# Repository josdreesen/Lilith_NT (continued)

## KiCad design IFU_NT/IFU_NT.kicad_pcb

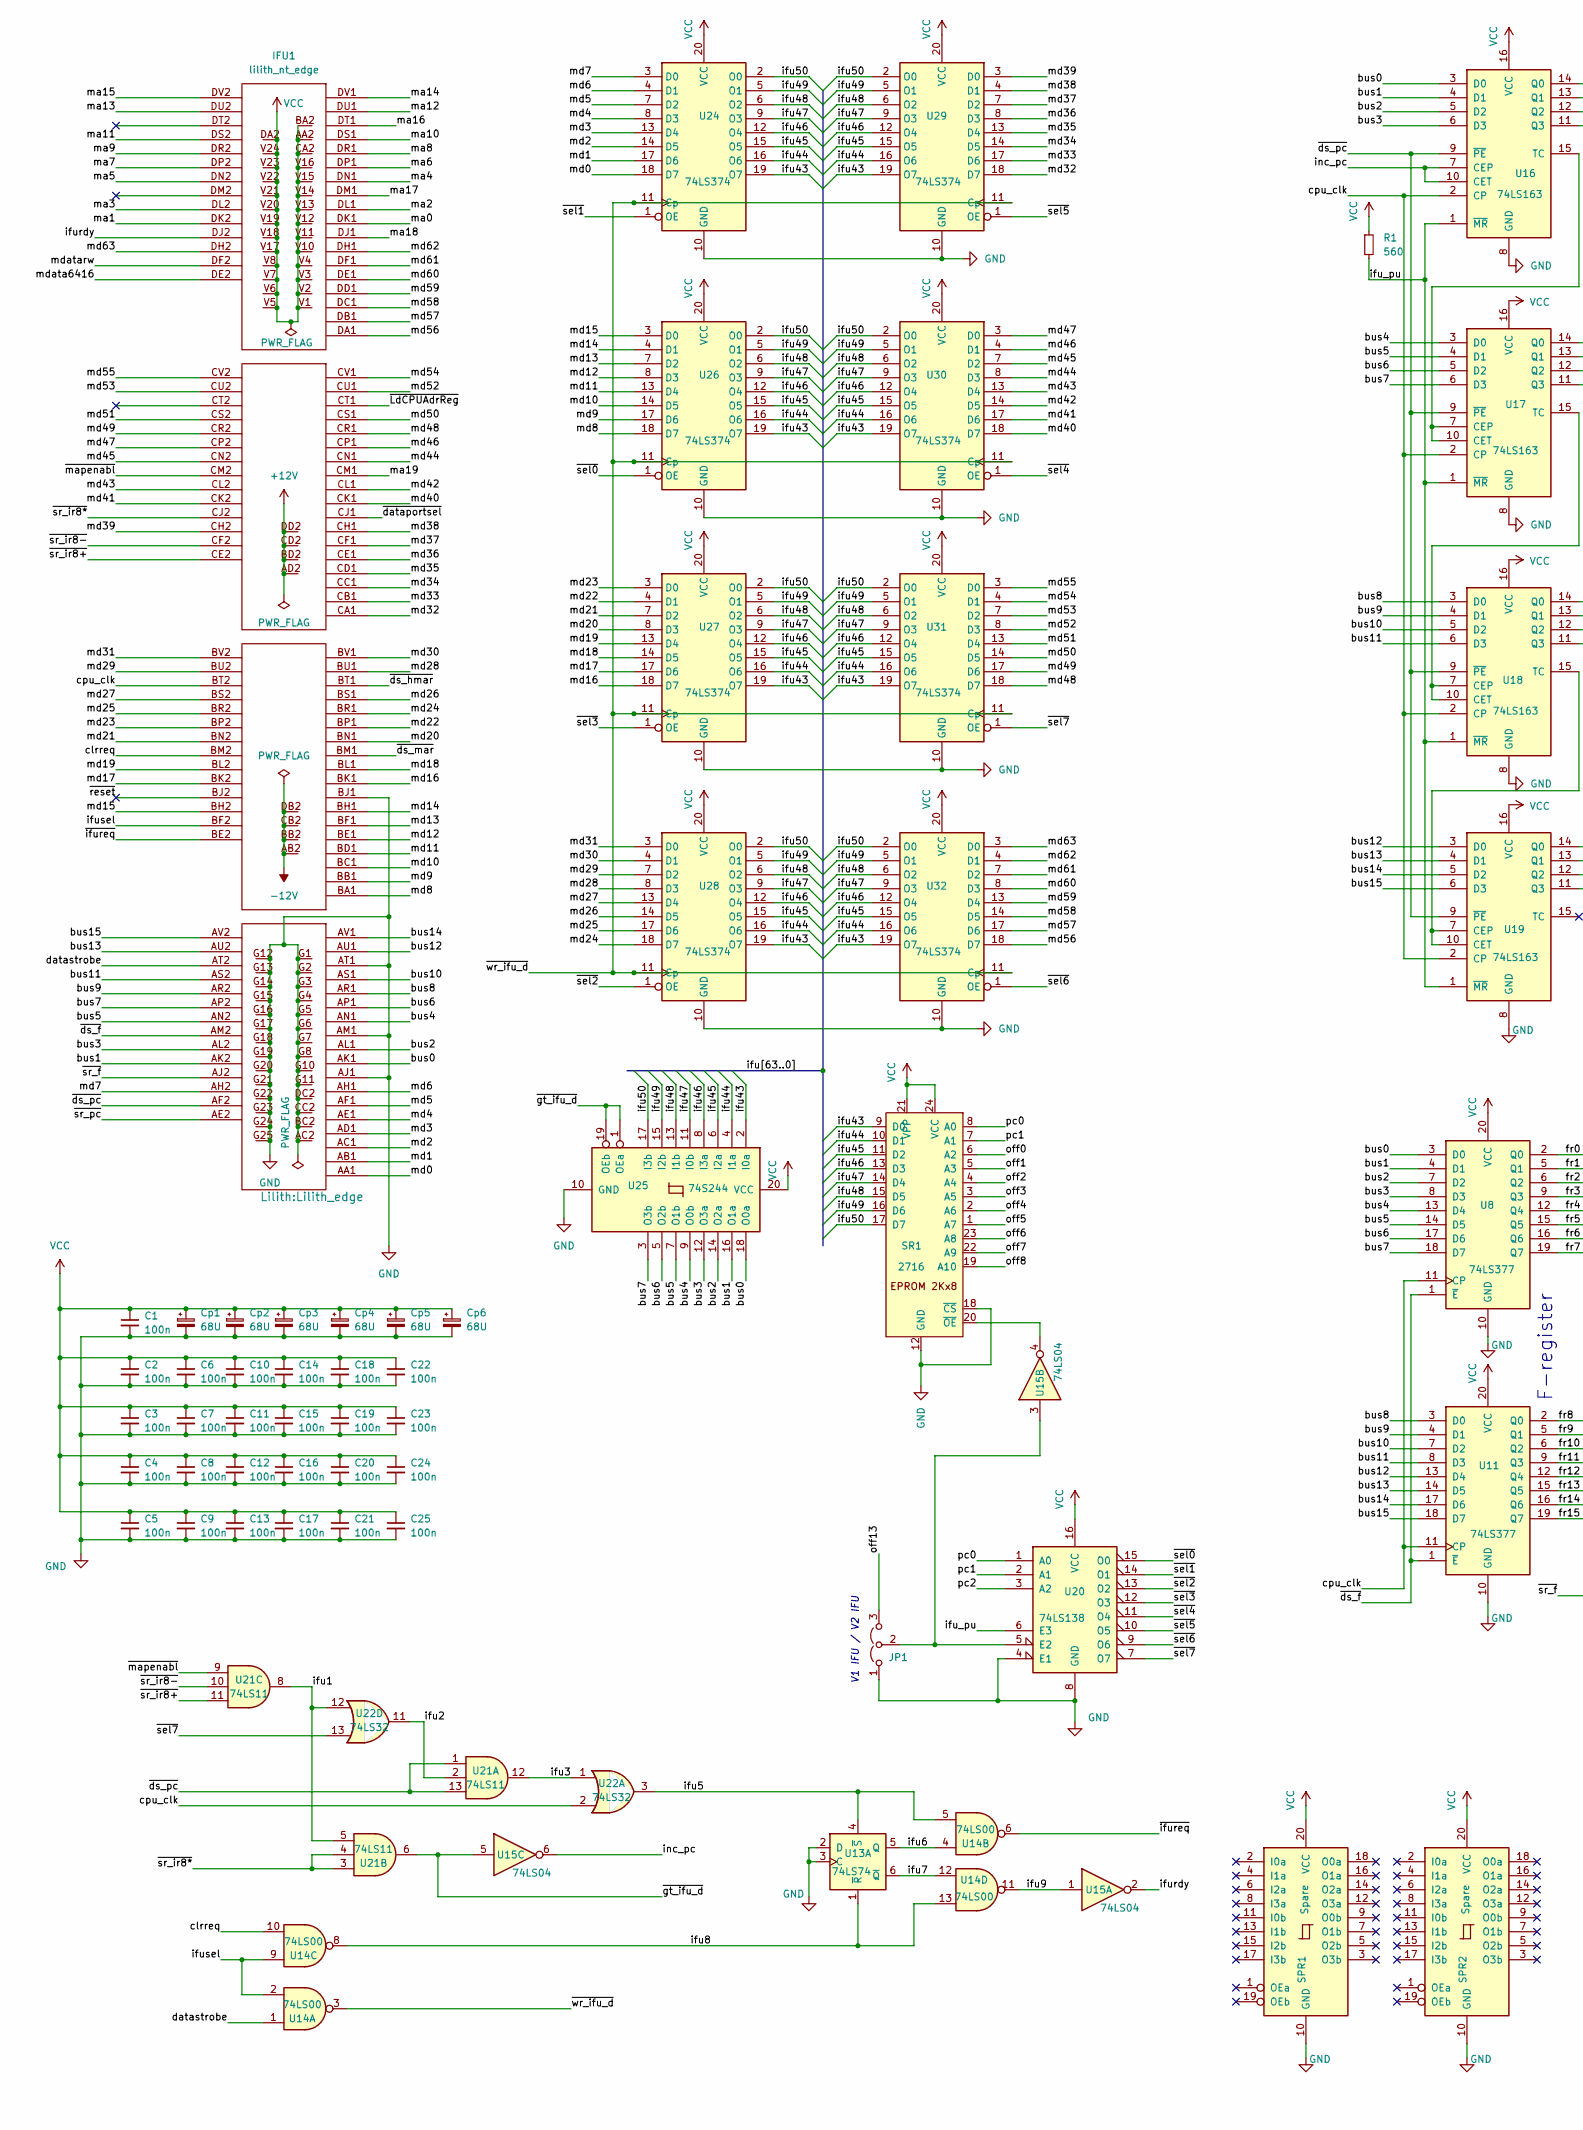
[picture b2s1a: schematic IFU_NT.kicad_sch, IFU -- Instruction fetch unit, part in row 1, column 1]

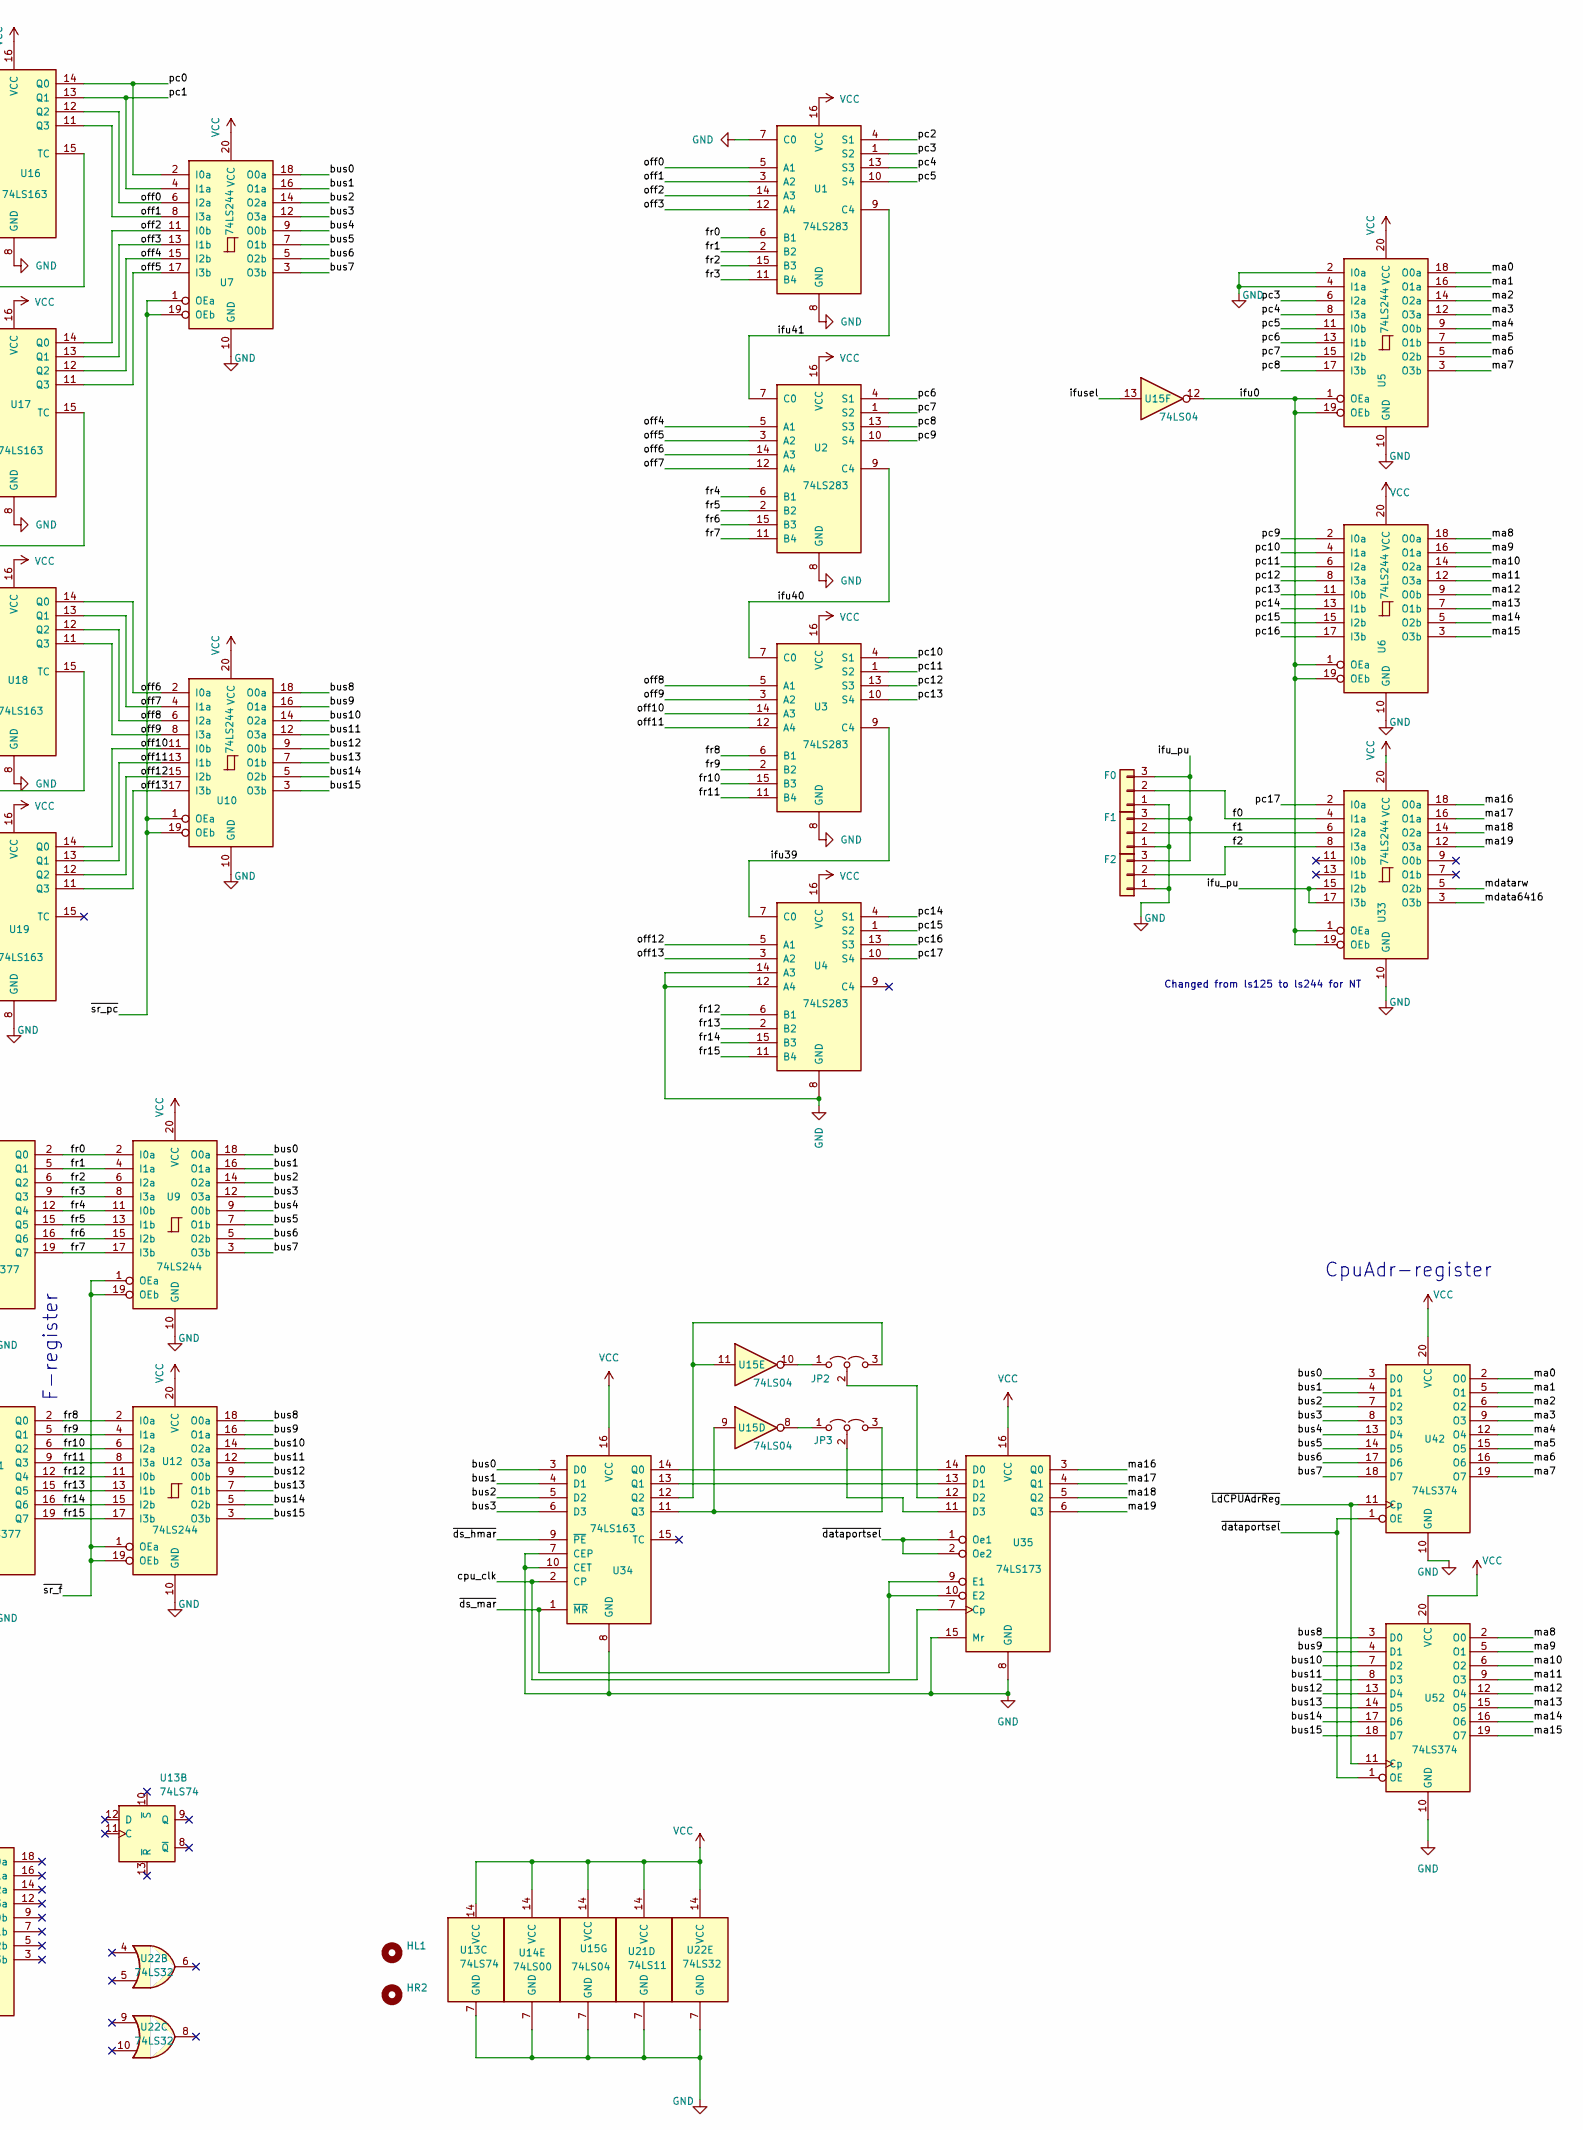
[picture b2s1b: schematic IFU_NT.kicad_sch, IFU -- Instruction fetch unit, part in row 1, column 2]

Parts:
C1, C2, C3, C4, C5, C6, C7, C8, C9, C10, C11, C12, C13, C14, C15, C16, C17, C18, C19, C20, C21, C22, C23, C24, C25: 100n; C_1206_3216Metric_Pad1.33x1.80mm_HandSolder
Cp1, Cp2, Cp3, Cp4, Cp5, Cp6: 68U; CP_PHP
F0, F1, F2: Conn_01x03; PinHeader_1x03_P2.54mm_Vertical
HL1: MountingHole; Handle
HR2: MountingHole; Handle
IFU1: lilith_nt_edge; Lilith_edge
JP1: Jumper_3_Open; PinSocket_1x03_P2.54mm_Vertical
JP2, JP3: Jumper_3_Open; PinHeader_1x03_P2.00mm_Vertical
R1: 560; R_Axial_DIN0207_L6.3mm_D2.5mm_P10.16mm_Horizontal
SPR1, SPR2: Spare; DIP-20_W7.62mm
SR1: 2716; DIP-24_W15.24mm_Socket
U1, U2, U3, U4: 74LS283; DIP-16_W7.62mm
U5, U6, U7, U9, U10, U12, U33: 74LS244; DIP-20_W7.62mm
U8, U11: 74LS377; DIP-20_W7.62mm
U13: 74LS74; DIP-14_W7.62mm
U14: 74LS00; DIP-14_W7.62mm
U15: 74LS04; DIP-14_W7.62mm
U16, U17, U18, U19, U34: 74LS163; DIP-16_W7.62mm
U20: 74LS138; DIP-16_W7.62mm
U21: 74LS11; DIP-14_W7.62mm
U22: 74LS32; DIP-14_W7.62mm
U24, U26, U27, U28, U29, U30, U31, U32, U42, U52: 74LS374; DIP-20_W7.62mm
U25: 74S244; DIP-20_W7.62mm
U35: 74LS173; DIP-16_W7.62mm

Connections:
+12V: IFU1.AD2, IFU1.BD2, IFU1.CD2, IFU1.DD2
-12V: IFU1.AB2, IFU1.BB2, IFU1.CB2, IFU1.DB2
/bus0: IFU1.AK1, U7.18 (O0a), U8.3 (D0), U9.18 (O0a), U16.3 (D0), U25.18 (O0a), U34.3 (D0), U42.3 (D0)
/bus1: IFU1.AK2, U7.16 (O1a), U8.4 (D1), U9.16 (O1a), U16.4 (D1), U25.16 (O1a), U34.4 (D1), U42.4 (D1)
/bus2: IFU1.AL1, U7.14 (O2a), U8.7 (D2), U9.14 (O2a), U16.5 (D2), U25.14 (O2a), U34.5 (D2), U42.7 (D2)
/bus3: IFU1.AL2, U7.12 (O3a), U8.8 (D3), U9.12 (O3a), U16.6 (D3), U25.12 (O3a), U34.6 (D3), U42.8 (D3)
/bus4: IFU1.AN1, U7.9 (O0b), U8.13 (D4), U9.9 (O0b), U17.3 (D0), U25.9 (O0b), U42.13 (D4)
/bus5: IFU1.AN2, U7.7 (O1b), U8.14 (D5), U9.7 (O1b), U17.4 (D1), U25.7 (O1b), U42.14 (D5)
/bus6: IFU1.AP1, U7.5 (O2b), U8.17 (D6), U9.5 (O2b), U17.5 (D2), U25.5 (O2b), U42.17 (D6)
/bus7: IFU1.AP2, U7.3 (O3b), U8.18 (D7), U9.3 (O3b), U17.6 (D3), U25.3 (O3b), U42.18 (D7)
/bus8: IFU1.AR1, U10.18 (O0a), U11.3 (D0), U12.18 (O0a), U18.3 (D0), U52.3 (D0)
/bus9: IFU1.AR2, U10.16 (O1a), U11.4 (D1), U12.16 (O1a), U18.4 (D1), U52.4 (D1)
/bus10: IFU1.AS1, U10.14 (O2a), U11.7 (D2), U12.14 (O2a), U18.5 (D2), U52.7 (D2)
/bus11: IFU1.AS2, U10.12 (O3a), U11.8 (D3), U12.12 (O3a), U18.6 (D3), U52.8 (D3)
/bus12: IFU1.AU1, U10.9 (O0b), U11.13 (D4), U12.9 (O0b), U19.3 (D0), U52.13 (D4)
/bus13: IFU1.AU2, U10.7 (O1b), U11.14 (D5), U12.7 (O1b), U19.4 (D1), U52.14 (D5)
/bus14: IFU1.AV1, U10.5 (O2b), U11.17 (D6), U12.5 (O2b), U19.5 (D2), U52.17 (D6)
/bus15: IFU1.AV2, U10.3 (O3b), U11.18 (D7), U12.3 (O3b), U19.6 (D3), U52.18 (D7)
/clrreq: IFU1.BM2, U14.10
/cpu_clk: IFU1.BT2, U8.11 (CP), U11.11 (CP), U16.2 (CP), U17.2 (CP), U18.2 (CP), U19.2 (CP), U22.2, U34.2 (CP), U35.7 (Cp)
/datastrobe: IFU1.AT2, U14.1
/f0: F0.2, U33.4 (I1a); also elsewhere on the board
/f1: F1.2, U33.6 (I2a); also elsewhere on the board
/f2: F2.2, U33.8 (I3a); also elsewhere on the board
/fr0: U1.6 (B1), U8.2 (Q0), U9.2 (I0a)
/fr1: U1.2 (B2), U8.5 (Q1), U9.4 (I1a)
/fr2: U1.15 (B3), U8.6 (Q2), U9.6 (I2a)
/fr3: U1.11 (B4), U8.9 (Q3), U9.8 (I3a)
/fr4: U2.6 (B1), U8.12 (Q4), U9.11 (I0b)
/fr5: U2.2 (B2), U8.15 (Q5), U9.13 (I1b)
/fr6: U2.15 (B3), U8.16 (Q6), U9.15 (I2b)
/fr7: U2.11 (B4), U8.19 (Q7), U9.17 (I3b)
/fr8: U3.6 (B1), U11.2 (Q0), U12.2 (I0a)
/fr9: U3.2 (B2), U11.5 (Q1), U12.4 (I1a)
/fr10: U3.15 (B3), U11.6 (Q2), U12.6 (I2a)
/fr11: U3.11 (B4), U11.9 (Q3), U12.8 (I3a)
/fr12: U4.6 (B1), U11.12 (Q4), U12.11 (I0b)
/fr13: U4.2 (B2), U11.15 (Q5), U12.13 (I1b)
/fr14: U4.15 (B3), U11.16 (Q6), U12.15 (I2b)
/fr15: U4.11 (B4), U11.19 (Q7), U12.17 (I3b)
/ifu0: U5.1 (OEa), U5.19 (OEb), U6.1 (OEa), U6.19 (OEb), U15.12, U33.1 (OEa), U33.19 (OEb)
/ifu1: U21.5, U21.8, U22.12
/ifu2: U21.2, U22.11
/ifu3: U21.12, U22.1
/ifu5: U13.4 (~S), U14.5, U22.3
/ifu6: U13.5 (Q), U14.4
/ifu7: U13.6 (~Q), U14.12
/ifu8: U13.1 (~R), U14.8, U14.13
/ifu9: U14.11, U15.1
/ifu39: U3.9 (C4), U4.7 (C0)
/ifu40: U2.9 (C4), U3.7 (C0)
/ifu41: U1.9 (C4), U2.7 (C0)
/ifu43: SR1.9 (D0), U24.19 (O7), U25.2 (I0a), U26.19 (O7), U27.19 (O7), U28.19 (O7), U29.19 (O7), U30.19 (O7), U31.19 (O7), U32.19 (O7)
/ifu44: SR1.10 (D1), U24.16 (O6), U25.4 (I1a), U26.16 (O6), U27.16 (O6), U28.16 (O6), U29.16 (O6), U30.16 (O6), U31.16 (O6), U32.16 (O6)
/ifu45: SR1.11 (D2), U24.15 (O5), U25.6 (I2a), U26.15 (O5), U27.15 (O5), U28.15 (O5), U29.15 (O5), U30.15 (O5), U31.15 (O5), U32.15 (O5)
/ifu46: SR1.13 (D3), U24.12 (O4), U25.8 (I3a), U26.12 (O4), U27.12 (O4), U28.12 (O4), U29.12 (O4), U30.12 (O4), U31.12 (O4), U32.12 (O4)
/ifu47: SR1.14 (D4), U24.9 (O3), U25.11 (I0b), U26.9 (O3), U27.9 (O3), U28.9 (O3), U29.9 (O3), U30.9 (O3), U31.9 (O3), U32.9 (O3)
/ifu48: SR1.15 (D5), U24.6 (O2), U25.13 (I1b), U26.6 (O2), U27.6 (O2), U28.6 (O2), U29.6 (O2), U30.6 (O2), U31.6 (O2), U32.6 (O2)
/ifu49: SR1.16 (D6), U24.5 (O1), U25.15 (I2b), U26.5 (O1), U27.5 (O1), U28.5 (O1), U29.5 (O1), U30.5 (O1), U31.5 (O1), U32.5 (O1)
/ifu50: SR1.17 (D7), U24.2 (O0), U25.17 (I3b), U26.2 (O0), U27.2 (O0), U28.2 (O0), U29.2 (O0), U30.2 (O0), U31.2 (O0), U32.2 (O0)
/ifu_pu: F0.3, F1.3, F2.3, R1.2, U16.1 (~MR), U17.1 (~MR), U18.1 (~MR), U19.1 (~MR), U20.6 (E3), U33.15 (I2b), U33.17 (I3b); also elsewhere on the board
/ifurdy: IFU1.DJ2, U15.2
/ifusel: IFU1.BF2, U14.2, U14.9, U15.13
/inc_pc: U15.6, U16.7 (CEP), U16.10 (CET)
/ma0: IFU1.DK1, U5.18 (O0a), U42.2 (O0)
/ma1: IFU1.DK2, U5.16 (O1a), U42.5 (O1)
/ma2: IFU1.DL1, U5.14 (O2a), U42.6 (O2)
/ma3: IFU1.DL2, U5.12 (O3a), U42.9 (O3)
/ma4: IFU1.DN1, U5.9 (O0b), U42.12 (O4)
/ma5: IFU1.DN2, U5.7 (O1b), U42.15 (O5)
/ma6: IFU1.DP1, U5.5 (O2b), U42.16 (O6)
/ma7: IFU1.DP2, U5.3 (O3b), U42.19 (O7)
/ma8: IFU1.DR1, U6.18 (O0a), U52.2 (O0)
/ma9: IFU1.DR2, U6.16 (O1a), U52.5 (O1)
/ma10: IFU1.DS1, U6.14 (O2a), U52.6 (O2)
/ma11: IFU1.DS2, U6.12 (O3a), U52.9 (O3)
/ma12: IFU1.DU1, U6.9 (O0b), U52.12 (O4)
/ma13: IFU1.DU2, U6.7 (O1b), U52.15 (O5)
/ma14: IFU1.DV1, U6.5 (O2b), U52.16 (O6)
/ma15: IFU1.DV2, U6.3 (O3b), U52.19 (O7)
/ma16: IFU1.DT1, U33.18 (O0a), U35.3 (Q0)
/ma17: IFU1.DM1, U33.16 (O1a), U35.4 (Q1)
/ma18: IFU1.DJ1, U33.14 (O2a), U35.5 (Q2)
/ma19: IFU1.CM1, U33.12 (O3a), U35.6 (Q3)
/md0: IFU1.AA1, U24.18 (D7)
/md1: IFU1.AB1, U24.17 (D6)
/md2: IFU1.AC1, U24.14 (D5)
/md3: IFU1.AD1, U24.13 (D4)
/md4: IFU1.AE1, U24.8 (D3)
/md5: IFU1.AF1, U24.7 (D2)
/md6: IFU1.AH1, U24.4 (D1)
/md7: IFU1.AH2, U24.3 (D0)
/md8: IFU1.BA1, U26.18 (D7)
/md9: IFU1.BB1, U26.17 (D6)
/md10: IFU1.BC1, U26.14 (D5)
/md11: IFU1.BD1, U26.13 (D4)
/md12: IFU1.BE1, U26.8 (D3)
/md13: IFU1.BF1, U26.7 (D2)
/md14: IFU1.BH1, U26.4 (D1)
/md15: IFU1.BH2, U26.3 (D0)
/md16: IFU1.BK1, U27.18 (D7)
/md17: IFU1.BK2, U27.17 (D6)
/md18: IFU1.BL1, U27.14 (D5)
/md19: IFU1.BL2, U27.13 (D4)
/md20: IFU1.BN1, U27.8 (D3)
/md21: IFU1.BN2, U27.7 (D2)
/md22: IFU1.BP1, U27.4 (D1)
/md23: IFU1.BP2, U27.3 (D0)
/md24: IFU1.BR1, U28.18 (D7)
/md25: IFU1.BR2, U28.17 (D6)
/md26: IFU1.BS1, U28.14 (D5)
/md27: IFU1.BS2, U28.13 (D4)
/md28: IFU1.BU1, U28.8 (D3)
/md29: IFU1.BU2, U28.7 (D2)
/md30: IFU1.BV1, U28.4 (D1)
/md31: IFU1.BV2, U28.3 (D0)
/md32: IFU1.CA1, U29.18 (D7)
/md33: IFU1.CB1, U29.17 (D6)
/md34: IFU1.CC1, U29.14 (D5)
/md35: IFU1.CD1, U29.13 (D4)
/md36: IFU1.CE1, U29.8 (D3)
/md37: IFU1.CF1, U29.7 (D2)
/md38: IFU1.CH1, U29.4 (D1)
/md39: IFU1.CH2, U29.3 (D0)
/md40: IFU1.CK1, U30.18 (D7)
/md41: IFU1.CK2, U30.17 (D6)
/md42: IFU1.CL1, U30.14 (D5)
/md43: IFU1.CL2, U30.13 (D4)
/md44: IFU1.CN1, U30.8 (D3)
/md45: IFU1.CN2, U30.7 (D2)
/md46: IFU1.CP1, U30.4 (D1)
/md47: IFU1.CP2, U30.3 (D0)
/md48: IFU1.CR1, U31.18 (D7)
/md49: IFU1.CR2, U31.17 (D6)
/md50: IFU1.CS1, U31.14 (D5)
/md51: IFU1.CS2, U31.13 (D4)
/md52: IFU1.CU1, U31.8 (D3)
/md53: IFU1.CU2, U31.7 (D2)
/md54: IFU1.CV1, U31.4 (D1)
/md55: IFU1.CV2, U31.3 (D0)
/md56: IFU1.DA1, U32.18 (D7)
/md57: IFU1.DB1, U32.17 (D6)
/md58: IFU1.DC1, U32.14 (D5)
/md59: IFU1.DD1, U32.13 (D4)
/md60: IFU1.DE1, U32.8 (D3)
/md61: IFU1.DF1, U32.7 (D2)
/md62: IFU1.DH1, U32.4 (D1)
/md63: IFU1.DH2, U32.3 (D0)
/mdata6416: IFU1.DE2, U33.3 (O3b)
/mdatarw: IFU1.DF2, U33.5 (O2b)
/off0: SR1.6 (A2), U1.5 (A1), U7.6 (I2a), U16.12 (Q2)
/off1: SR1.5 (A3), U1.3 (A2), U7.8 (I3a), U16.11 (Q3)
/off2: SR1.4 (A4), U1.14 (A3), U7.11 (I0b), U17.14 (Q0)
/off3: SR1.3 (A5), U1.12 (A4), U7.13 (I1b), U17.13 (Q1)
/off4: SR1.2 (A6), U2.5 (A1), U7.15 (I2b), U17.12 (Q2)
/off5: SR1.1 (A7), U2.3 (A2), U7.17 (I3b), U17.11 (Q3)
/off6: SR1.23 (A8), U2.14 (A3), U10.2 (I0a), U18.14 (Q0)
/off7: SR1.22 (A9), U2.12 (A4), U10.4 (I1a), U18.13 (Q1)
/off8: SR1.19 (A10), U3.5 (A1), U10.6 (I2a), U18.12 (Q2)
/off9: U3.3 (A2), U10.8 (I3a), U18.11 (Q3)
/off10: U3.14 (A3), U10.11 (I0b), U19.14 (Q0)
/off11: U3.12 (A4), U10.13 (I1b), U19.13 (Q1)
/off12: U4.5 (A1), U10.15 (I2b), U19.12 (Q2)
/off13: JP1.3 (B), U4.3 (A2), U10.17 (I3b), U19.11 (Q3)
/pc0: SR1.8 (A0), U7.2 (I0a), U16.14 (Q0), U20.1 (A0)
/pc1: SR1.7 (A1), U7.4 (I1a), U16.13 (Q1), U20.2 (A1)
/pc2: U1.4 (S1), U20.3 (A2)
/pc3: U1.1 (S2), U5.6 (I2a)
/pc4: U1.13 (S3), U5.8 (I3a)
/pc5: U1.10 (S4), U5.11 (I0b)
/pc6: U2.4 (S1), U5.13 (I1b)
/pc7: U2.1 (S2), U5.15 (I2b)
/pc8: U2.13 (S3), U5.17 (I3b)
/pc9: U2.10 (S4), U6.2 (I0a)
/pc10: U3.4 (S1), U6.4 (I1a)
/pc11: U3.1 (S2), U6.6 (I2a)
/pc12: U3.13 (S3), U6.8 (I3a)
/pc13: U3.10 (S4), U6.11 (I0b)
/pc14: U4.4 (S1), U6.13 (I1b)
/pc15: U4.1 (S2), U6.15 (I2b)
/pc16: U4.13 (S3), U6.17 (I3b)
/pc17: U4.10 (S4), U33.2 (I0a)
/~LdCPUAdrReg: IFU1.CT1, U42.11 (Cp), U52.11 (Cp)
/~dataportsel: IFU1.CJ1, U35.1 (Oe1), U35.2 (Oe2), U42.1 (OE), U52.1 (OE)
/~ds_f: IFU1.AM2, U8.1 (~E), U11.1 (~E)
/~ds_hmar: IFU1.BT1, U34.9 (~PE)
/~ds_mar: IFU1.BM1, U34.1 (~MR), U35.9 (E1), U35.10 (E2)
/~ds_pc: IFU1.AF2, U16.9 (~PE), U17.9 (~PE), U18.9 (~PE), U19.9 (~PE), U21.1, U21.13
/~gt_ifu_d: U15.5, U21.6, U25.1 (OEa), U25.19 (OEb)
/~ifureq: IFU1.BE2, U14.6
/~mapenabl: IFU1.CM2, U21.9
/~reset: IFU1.BJ2
/~sel0: U20.15 (O0), U26.1 (OE)
/~sel1: U20.14 (O1), U24.1 (OE)
/~sel2: U20.13 (O2), U28.1 (OE)
/~sel3: U20.12 (O3), U27.1 (OE)
/~sel4: U20.11 (O4), U30.1 (OE)
/~sel5: U20.10 (O5), U29.1 (OE)
/~sel6: U20.9 (O6), U32.1 (OE)
/~sel7: U20.7 (O7), U22.13, U31.1 (OE)
/~sr_f: IFU1.AJ2, U9.1 (OEa), U9.19 (OEb), U12.1 (OEa), U12.19 (OEb)
/~sr_ir8*: IFU1.CJ2, U21.3, U21.4
/~sr_ir8+: IFU1.CE2, U21.11
/~sr_ir8-: IFU1.CF2, U21.10
/~sr_pc: IFU1.AE2, U7.1 (OEa), U7.19 (OEb), U10.1 (OEa), U10.19 (OEb)
/~wr_ifu_d: U14.3, U24.11 (Cp), U26.11 (Cp), U27.11 (Cp), U28.11 (Cp), U29.11 (Cp), U30.11 (Cp), U31.11 (Cp), U32.11 (Cp)
GND: C1.2, C2.2, C3.2, C4.2, C5.2, C6.2, C7.2, C8.2, C9.2, C10.2, C11.2, C12.2, C13.2, C14.2, C15.2, C16.2, C17.2, C18.2, C19.2, C20.2, C21.2, C22.2, C23.2, C24.2, C25.2, Cp1.2, Cp2.2, Cp3.2, Cp4.2, Cp5.2, Cp6.2, F0.1, F1.1, F2.1, IFU1.AC2, IFU1.AJ1, IFU1.AM1, IFU1.AT1, IFU1.BC2, IFU1.BJ1, IFU1.CC2, IFU1.DC2, IFU1.G1 (GND), IFU1.G2 (GND), IFU1.G3 (GND), IFU1.G4 (GND), IFU1.G5 (GND), IFU1.G6 (GND), IFU1.G7 (GND), IFU1.G8 (GND), IFU1.G10, IFU1.G11, IFU1.G12, IFU1.G13, IFU1.G14, IFU1.G15, IFU1.G16, IFU1.G17, IFU1.G18, IFU1.G19, IFU1.G20, IFU1.G21, IFU1.G22, IFU1.G23, IFU1.G24, IFU1.G25, JP1.1 (A), SPR1.10 (GND), SPR2.10 (GND), SR1.12 (GND), SR1.18 (~CS), U1.7 (C0), U1.8 (GND), U2.8 (GND), U3.8 (GND), U4.8 (GND), U4.12 (A4), U4.14 (A3), U5.2 (I0a), U5.4 (I1a), U5.10 (GND), U6.10 (GND), U7.10 (GND), U8.10 (GND), U9.10 (GND), U10.10 (GND), U11.10 (GND), U12.10 (GND), U13.2 (D), U13.3 (C), U13.7 (GND), U14.7 (GND), U15.7 (GND), U16.8 (GND), U17.8 (GND), U18.8 (GND), U19.8 (GND), U20.4 (E1), U20.8 (GND), U21.7 (GND), U22.7 (GND), U24.10 (GND), U25.10 (GND), U26.10 (GND), U27.10 (GND), U28.10 (GND), U29.10 (GND), U30.10 (GND), U31.10 (GND), U32.10 (GND), U33.10 (GND), U34.7 (CEP), U34.8 (GND), U34.10 (CET), U35.8 (GND), U35.15 (Mr), U42.10 (GND), U52.10 (GND); also elsewhere on the board
unnamed: JP1.2 (C), U15.3, U20.5 (E2)
unnamed: JP2.1 (A), U15.10
unnamed: JP2.3 (B), U15.11, U34.12 (Q2)
unnamed: JP2.2 (C), U35.12 (D2)
unnamed: JP3.1 (A), U15.8
unnamed: JP3.3 (B), U15.9, U34.11 (Q3)
unnamed: JP3.2 (C), U35.11 (D3)
unnamed: SR1.20 (~OE), U15.4
unnamed: U16.15 (TC), U17.7 (CEP), U17.10 (CET)
unnamed: U17.15 (TC), U18.7 (CEP), U18.10 (CET)
unnamed: U18.15 (TC), U19.7 (CEP), U19.10 (CET)
unnamed: U34.14 (Q0), U35.14 (D0)
unnamed: U34.13 (Q1), U35.13 (D1)
VCC: C1.1, C2.1, C3.1, C4.1, C5.1, C6.1, C7.1, C8.1, C9.1, C10.1, C11.1, C12.1, C13.1, C14.1, C15.1, C16.1, C17.1, C18.1, C19.1, C20.1, C21.1, C22.1, C23.1, C24.1, C25.1, Cp1.1, Cp2.1, Cp3.1, Cp4.1, Cp5.1, Cp6.1, IFU1.AA2, IFU1.BA2, IFU1.CA2, IFU1.DA2, IFU1.V1 (VCC), IFU1.V2 (VCC), IFU1.V3 (VCC), IFU1.V4 (VCC), IFU1.V5 (VCC), IFU1.V6 (VCC), IFU1.V7 (VCC), IFU1.V8 (VCC), IFU1.V10, IFU1.V11, IFU1.V12, IFU1.V13, IFU1.V14, IFU1.V15, IFU1.V16, IFU1.V17, IFU1.V18, IFU1.V19, IFU1.V20, IFU1.V21, IFU1.V22, IFU1.V23, IFU1.V24, R1.1, SPR1.20 (VCC), SPR2.20 (VCC), SR1.21 (VPP), SR1.24 (VCC), U1.16 (VCC), U2.16 (VCC), U3.16 (VCC), U4.16 (VCC), U5.20 (VCC), U6.20 (VCC), U7.20 (VCC), U8.20 (VCC), U9.20 (VCC), U10.20 (VCC), U11.20 (VCC), U12.20 (VCC), U13.14 (VCC), U14.14 (VCC), U15.14 (VCC), U16.16 (VCC), U17.16 (VCC), U18.16 (VCC), U19.16 (VCC), U20.16 (VCC), U21.14 (VCC), U22.14 (VCC), U24.20 (VCC), U25.20 (VCC), U26.20 (VCC), U27.20 (VCC), U28.20 (VCC), U29.20 (VCC), U30.20 (VCC), U31.20 (VCC), U32.20 (VCC), U33.20 (VCC), U34.16 (VCC), U35.16 (VCC), U42.20 (VCC), U52.20 (VCC)

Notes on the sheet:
Changed from ls125 to ls244 for NT
V1 IFU / V2 IFU
F-register
CpuAdr-register

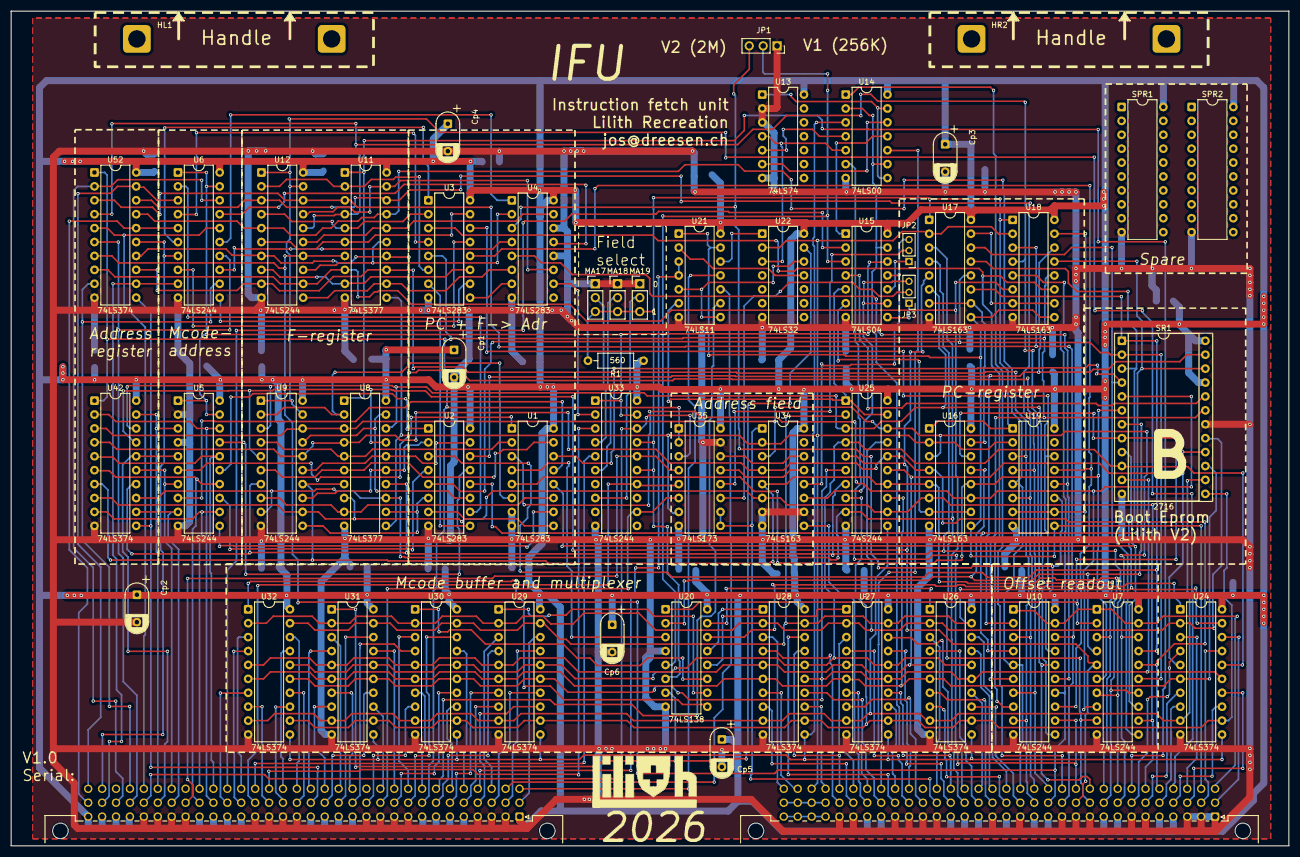
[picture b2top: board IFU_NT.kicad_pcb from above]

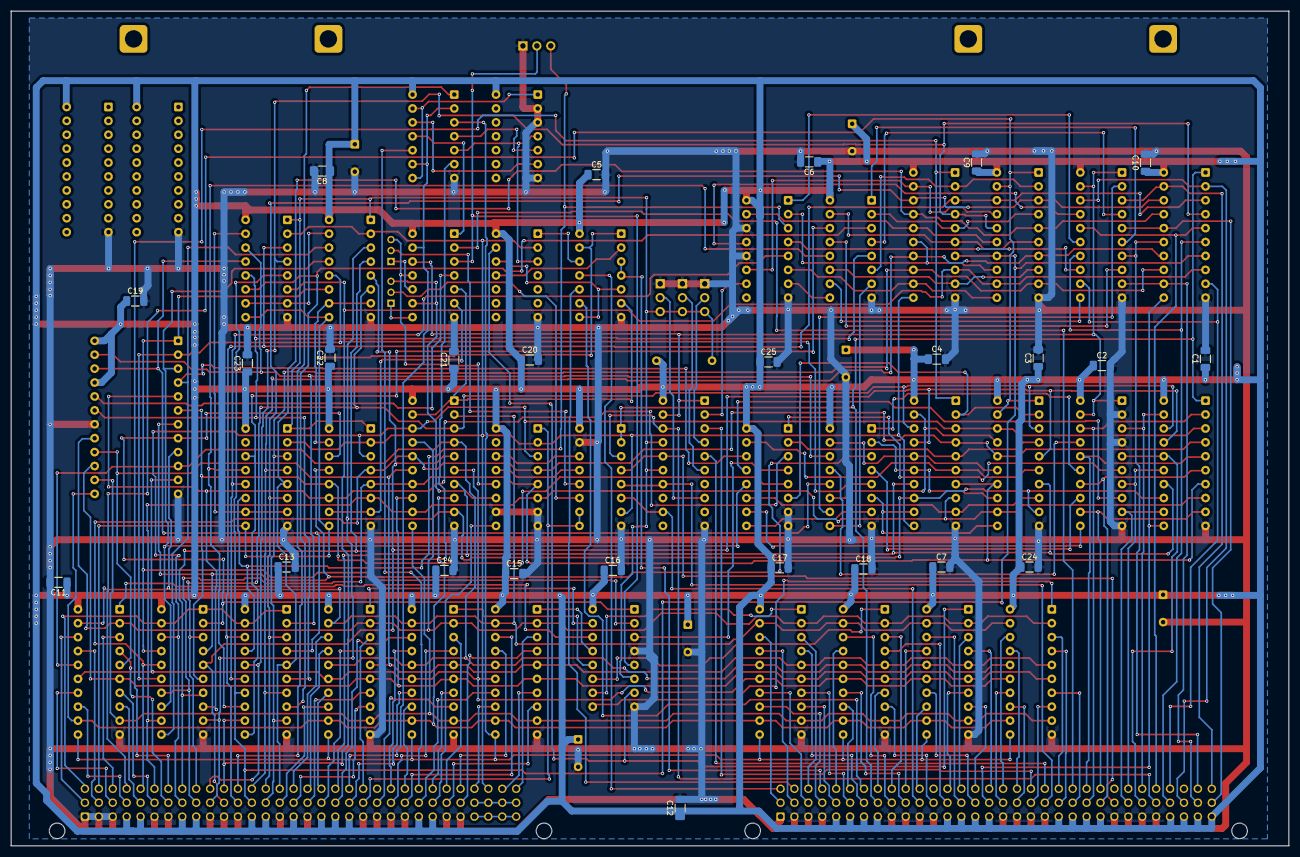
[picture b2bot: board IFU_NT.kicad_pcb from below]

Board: 2 copper layers, 233.3 x 152.4 mm, 80 parts (25 on the bottom side), 220 nets.

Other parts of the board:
MA17, MA18, MA19: Conn_01x03; PinHeader_1x03_P2.54mm_Vertical

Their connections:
/f0: MA17.2; also elsewhere on the board
/f1: MA18.2; also elsewhere on the board
/f2: MA19.2; also elsewhere on the board
/ifu_pu: MA17.3, MA18.3, MA19.3; also elsewhere on the board
GND: MA17.1, MA18.1, MA19.1; also elsewhere on the board
